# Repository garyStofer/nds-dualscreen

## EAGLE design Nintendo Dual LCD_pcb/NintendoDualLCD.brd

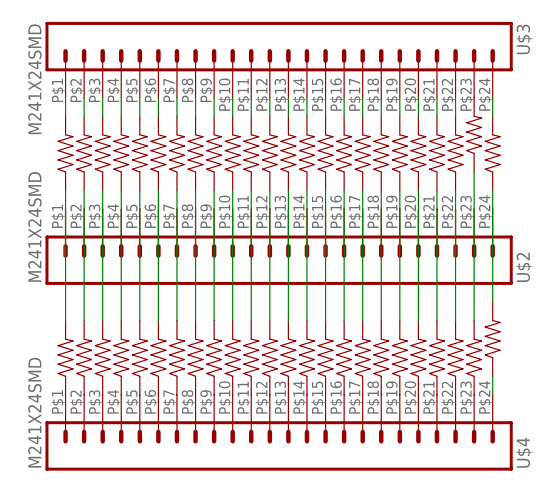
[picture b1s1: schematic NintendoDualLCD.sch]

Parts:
R1, R2, R3, R4, R5, R6, R7, R8, R9, R10, R11, R12, R13, R14, R15, R16, R17, R18, R19, R20, R21, R22, R23, R24, R25, R26, R27, R28, R29, R30, R31, R32, R33, R34, R35, R36, R37, R38, R39, R40, R41, R42, R43, R44, R45, R46, R47, R48: 100; 0603-RES
U$2, U$3, U$4: M241X24SMD; 1X24SMD

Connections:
unnamed: R1.1, R23.2, U$2.P$1 (2)
unnamed: R2.1, R24.2, U$2.P$2 (3)
unnamed: R3.1, R25.2, U$2.P$3 (4)
unnamed: R4.1, R26.2, U$2.P$4 (5)
unnamed: R5.1, R27.2, U$2.P$5 (6)
unnamed: R6.1, R28.2, U$2.P$6 (7)
unnamed: R7.1, R29.2, U$2.P$7 (8)
unnamed: R8.1, R30.2, U$2.P$8 (9)
unnamed: R9.1, R31.2, U$2.P$9 (10)
unnamed: R10.1, R32.2, U$2.P$10 (11)
unnamed: R11.1, R34.2, U$2.P$11 (12)
unnamed: R12.1, R35.2, U$2.P$12 (13)
unnamed: R13.1, R36.2, U$2.P$13 (14)
unnamed: R14.1, R37.2, U$2.P$14 (15)
unnamed: R15.1, R38.2, U$2.P$15 (16)
unnamed: R16.1, R39.2, U$2.P$16 (17)
unnamed: R17.1, R40.2, U$2.P$17 (18)
unnamed: R18.1, R41.2, U$2.P$18 (19)
unnamed: R19.1, R42.2, U$2.P$19 (20)
unnamed: R20.1, R43.2, U$2.P$20 (21)
unnamed: R1.2, U$3.P$1 (2)
unnamed: R2.2, U$3.P$2 (3)
unnamed: R3.2, U$3.P$3 (4)
unnamed: R4.2, U$3.P$4 (5)
unnamed: R5.2, U$3.P$5 (6)
unnamed: R6.2, U$3.P$6 (7)
unnamed: R7.2, U$3.P$7 (8)
unnamed: R8.2, U$3.P$8 (9)
unnamed: R9.2, U$3.P$9 (10)
unnamed: R10.2, U$3.P$10 (11)
unnamed: R11.2, U$3.P$11 (12)
unnamed: R12.2, U$3.P$12 (13)
unnamed: R13.2, U$3.P$13 (14)
unnamed: R14.2, U$3.P$14 (15)
unnamed: R15.2, U$3.P$15 (16)
unnamed: R16.2, U$3.P$16 (17)
unnamed: R17.2, U$3.P$17 (18)
unnamed: R18.2, U$3.P$18 (19)
unnamed: R19.2, U$3.P$19 (20)
unnamed: R20.2, U$3.P$20 (21)
unnamed: R21.1, R44.2, U$2.P$21 (22)
unnamed: R21.2, U$3.P$21 (22)
unnamed: R22.1, R45.2, U$2.P$22 (23)
unnamed: R22.2, U$3.P$22 (23)
unnamed: R25.1, U$4.P$3 (4)
unnamed: R26.1, U$4.P$4 (5)
unnamed: R27.1, U$4.P$5 (6)
unnamed: R28.1, U$4.P$6 (7)
unnamed: R29.1, U$4.P$7 (8)
unnamed: R30.1, U$4.P$8 (9)
unnamed: R31.1, U$4.P$9 (10)
unnamed: R32.1, U$4.P$10 (11)
unnamed: R34.1, U$4.P$11 (12)
unnamed: R36.1, U$4.P$13 (14)
unnamed: R37.1, U$4.P$14 (15)
unnamed: R38.1, U$4.P$15 (16)
unnamed: R39.1, U$4.P$16 (17)
unnamed: R40.1, U$4.P$17 (18)
unnamed: R41.1, U$4.P$18 (19)
unnamed: R42.1, U$4.P$19 (20)
unnamed: R43.1, U$4.P$20 (21)
unnamed: R44.1, U$4.P$21 (22)
unnamed: R45.1, U$4.P$22 (23)
unnamed: R23.1, U$4.P$1 (2)
unnamed: R24.1, U$4.P$2 (3)
unnamed: R35.1, U$4.P$12 (13)
unnamed: R46.2, U$3.P$23 (24)
unnamed: R33.1, U$4.P$23 (24)
unnamed: R47.1, R48.2, U$2.P$24 (25)
unnamed: R48.1, U$4.P$24 (25)
unnamed: R33.2, R46.1, U$2.P$23 (24)
unnamed: R47.2, U$3.P$24 (25)

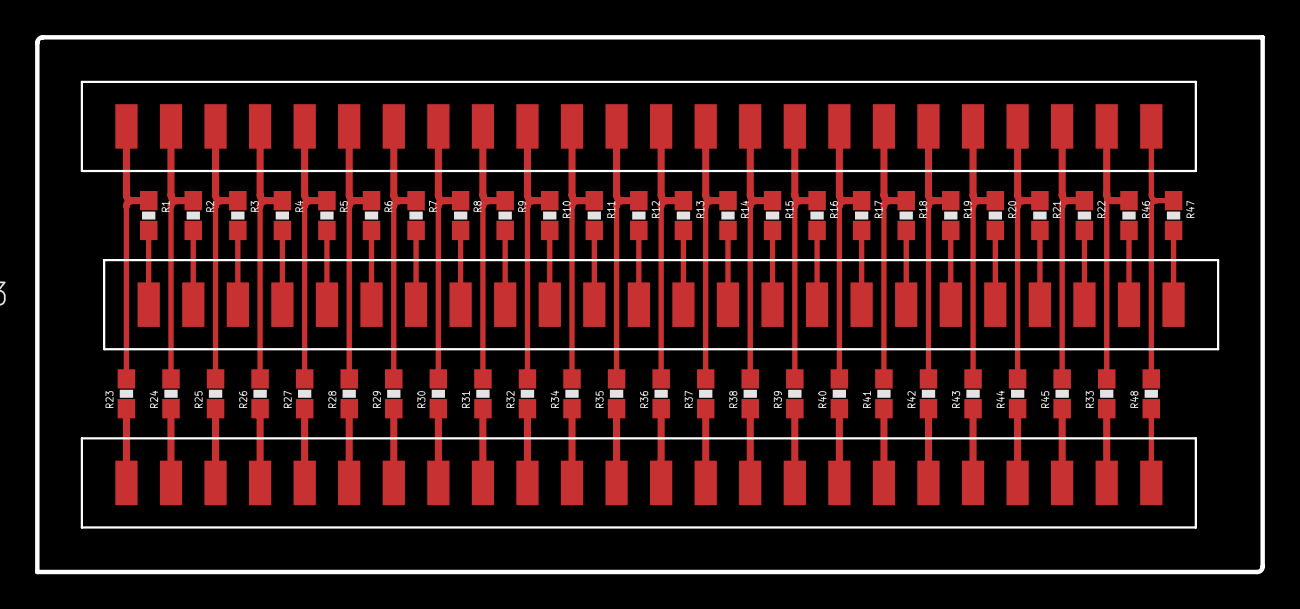
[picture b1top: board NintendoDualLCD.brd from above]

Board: 2 copper layers, 69.8 x 30.5 mm, 51 parts (0 on the bottom side), 72 nets.

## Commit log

2015-01-15 Main verilog file initial version
2015-01-15 moved file main2.v into Xilinx_Verilog subfolder
2015-01-15 removed unnecessary files -- added a wiring readme file
2015-01-15 this is the doc for the NDS original screen
2015-01-29 fixed the screen jumping while using the wireless communication by syncing the NEC screens on the nds v-sync instead of some time after it.
2015-06-19 Migrating wiki contents from Google Code

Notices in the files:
parts and their libraries:
SparkFun-Connectors: Licensing: CC v3.0 Share-Alike You are welcome to use this library for commercial purposes.
